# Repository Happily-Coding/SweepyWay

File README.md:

# SweepyWay Split Keyboard 

A truly ergonomic, begginner friendly keyboard.

<details open><summary><h2 style="display:inline-block">Photos & Outputs</h2></summary>

left side | right side
-|-
 | 

[More outputs](https://happily-coding.github.io/SweepyWay/filtered-output/) (images, pdfs, stl 3d models, etc)

<details><summary><h3 style="display:inline-block"> 3D Preview</h3></summary>

The 3D preview shows how the keyboard looks with all components in place (switches, diodes, MCU, and keycaps).

### 3D Model Files

#### Interactive 3D View (STL Format)
- [Left PCB STL](https://happily-coding.github.io/SweepyWay/filtered-output/pcbs/3d/left_pcb-3d.stl) 🎮
- [Right PCB STL](https://happily-coding.github.io/SweepyWay/filtered-output/pcbs/3d/right_pcb-3d.stl) 🎮

> 🎮 **How to View**: Click the links above, then GitHub will automatically render the STL files in an interactive 3D viewer. You can rotate, zoom, and pan using your mouse.

#### Markdown Rendering (ASCII STL)
The ASCII STL files are generated in the workflow and embedded in markdown using the ```stl code block syntax. GitHub renders these automatically when viewing the README.

> 💡 **Note**: The ASCII STL files are generated from the binary STL files in the workflow and embedded directly in this README for instant rendering.

#### STEP Files (CAD Exchange)
- [Left PCB STEP file](https://happily-coding.github.io/SweepyWay/filtered-output/pcbs/3d/left_pcb-3d.step) 🔧
- [Right PCB STEP file](https://happily-coding.github.io/SweepyWay/filtered-output/pcbs/3d/right_pcb-3d.step) 🔧

> ⚠️ **Note**: GitHub doesn't render STEP files directly. Use these for CAD software:
> - Download and open in KiCad 3D viewer, FreeCAD, Fusion 360, etc.
> - Use online STEP viewers like [3DViewer.net](https://3dviewer.net/)
> - Convert to STL format for GitHub rendering

### 3D Rendered Images

left side | right side
-|-
 | 
 | 

### Troubleshooting Missing Components

If the 3D renders show only the PCB without components, the environment variables may not be properly set. The PCB files use `${PATH_TO_SWEEPYWAY_COMPONENT_MODELS}` but KiCad 9 also needs `KICAD9_3DMODEL_DIR`.

**Solution**: Set BOTH environment variables to the same path:
```bash
PATH_TO_SWEEPYWAY_COMPONENT_MODELS="/path/to/component_3d_models" \
KICAD9_3DMODEL_DIR="/path/to/component_3d_models" \
kibot -c kibot/3d_preview.kibot.yaml
```

**GitHub Actions**: The workflow now sets both variables to `${{ github.workspace }}/component_3d_models`

**Verification**: Check that:
1. `component_3d_models/` directory exists
2. All required STEP files are present: `Choc_V1_Hotswap.step`, `Choc_V1_Switch.step`, `Choc_V1_Keycap_MBK_White_1u.step`, etc.
3. The Docker container has access to the models directory

</details>

<details><summary><h3 style="display:inline-block"> Output details</h2></summary>
- Cases contains 3d models (not only of the case), l_cover is the plate that holds the switches firmly in place, and houses the controller and battery, protecting them
<!-- 
?v=1 was used to force the update of the cache from github (it could have been any parameter)
 | 
-->
</details>

<details open><summary><h2 style="display:inline-block">Features</span></summary> 

* **Beginner friendly**
  * Available pdfs, so you can print the layout and see how it feels
  * Abundant keys, but in non disruptive places.
  * No soldering required (WIP)
* **Truly ergonomic**
  * Aggressive column stagger, like Ferris Sweep, to match how fingers are staggered.
  * Choc V1 keys
    * Very low actuation force switches available (example: nocturnal)
    * Low profile (seamless use without handrest, easier to adjust height without an adjustable desk)
    * ChocV1 spacing (reach the outer columns with less over-stretching)
  * Tenting, negative tilting, adjustable height and hand rest solutions (WIP)
* **Energy efficient**
  * [Nice!nano](https://nicekeyboards.com/nice-nano) optimised, but any promicro should work (bottom up) 
  <!-- * [Nice!view](https://nicekeyboards.com/nice-view) support Not tested, probably requires small modifications --> 
  * No leds
* **Accident prepared** 
  * Controller far away from accidental splash zones,
  * Power switch for transport
  * No metal plates to help prevent static discharge from friying the keyboard
  * Hotswappable battery, switches, keycaps, controller, and case. Replace anything that breaks or you dislike.
    * You can even remove the components and use them with a different pcb.
* **Easy to modify** (Declarative design done via yaml)
  * Layout is declared using [Ergogen](https://github.com/mrzealot/ergogen/). 
  * Uses Ergogen to translate YAML to a KiCad PCB and plate files for FR-4 fab or laser cutting
  * Uses Ergogen to output jscad files for the case, and openjscad to convert them to stl.
  * Uses [kicad-automation-scripts](https://github.com/productize/kicad-automation-scripts) and [FreeRouting](https://github.com/freerouting/freerouting) to **automatically route the traces on the PCB**
  * Uses [KiKit](https://github.com/yaqwsx/KiKit) to render PCB previews and production-ready **Gerber files**
  * Uses [Trimesh](https://github.com/mikedh/trimesh/tree/main) to parametrically create a palm rest for the keyboard shape.
  * Uses Kibot to produce jlpcb pos files and BOM so you can order your pcb assembled and not have to solder. (WIP) 
  * Compatible with [no solder spring headers](https://typeractive.xyz/products/no-solder-spring-headers) 

<details><summary><h2 style="display:inline-block"> Work in progress. TODO List</h2></summary>

- perfect top case, and replicate for right side
  - the controller area is delicate, we need to only increase height on the part that the controller and maybe the jsph and reset switch are, since otherwise they wont fit with the plate cutting into them
  - We need to keep the reset butotn exposed to the outside if we want to be able to use the keyboard flash with the cover on (which may be important for typing)
- add the battery and microcontroller 3d model to check there are no issues
- add a lengua in the wall of the case below the top plate to en sure no drainage on the corners?
- Add parametric tenting legs.
- Add spacing between case wall and pcb (add some more padding in addition to the wall thickness)
- Finish making hand rest parametric and integrate it into the pipeline
- Fix the additional outline to cover the controller
- make sure the bom & pos are outputed correctly and ideally automated
- Nice haves:
  - Make base tilting and tenting compatible and or adjustable height
  - add water draining holes
  - Add a piece of plastic that goes inward from the top of the border and fits in it to cover the pcb
  - add leds and spacing for a big batery in the tenting solution
  - add other controller types
  - improve controller pin assignment for better routing
  - Add headers soldering from jlpcb
  - add a tenting system with space for a larger batery or make space for a larger batery in the palm rest, so you can reasonably use the keyboard with rgb.
  - Add row staggered variants that are space efficient.
  - Make sure the keyboard is correctly produced with mbk spacing, and mx spacing.
  - Add the ability to customize keycap spacing for the outer columns and rows
</details>

<details><summary><h2 style="display:inline-block"> How to modify it</h2></summary>

### Setup
If you would like to modify this:
* fork it
* clone it locally with celoide submodule git clone --recurse-submodules https://github.com/Happily-Coding/SweepyWay.git
* change `ergogen/config.yaml` to your liking
* to test it locally if you have node, you can run npm npm i -g ergogen or just npm install from the directory of the repo.
* to be able to view the 3d models in kicad you need go to the top menu -> preferences -> path and add the value for PATH_TO_SWEEPYWAY_COMPONENT_MODELS, which should be the location of your 3d models folder for example C:\Users\YourName\KeyboardDesign\SweepyWay\component_3d_models. Then, after opening kicad , you can open the 3d viewer in the toolbar (or using alt 3).
* to be able to open individual step or stl files, i find [this page](https://3dviewer.net/index.html) comfortable
* to understand what each definition in ergogen ends up creating open the link to the repo [here ](https://ergogen.xyz/)
* reactivate github workflows
* reactivate github pages at https://github.com/your-name/your-repo/settings/pages, choose github actions instead of a branch
* push your changes; the `build.yml` GitHub Workflows(https://github.com/your-name/your-repo/actions) will pick it up, autoroute and generate Gerbers, all in a zip file, and then deploy it to github pages(https://your-name.github.io/your-repo/).
* or:
  * make sure to have Docker CLI and NodeJS installed
  * run `make setup clean all`
  * check the `output` folder for KiCad PCBs and Gerbers
* you can find the latest build artifacts [here](https://happily-coding.github.io/SweepyWay/)

See the [workflow](.github/workflows/build.yml) or the [Makefile](Makefile) for more details.

### Quickly previewing the pcb before pushing
Open the project, open a terminal, run ```cd ergogen``` and ```ergogen .```

### Quickly previewing the case and other jscad files before pushing
Open [neorama openjscad](https://neorama.de/) , and drag the jscad file to the button, you can pan and move using right click or shift rightclick.

### Quickly previewing the palmrest before pushing
- Install uv ```pip install uv``` and run uv sync to generate your virtual environment (only once)
- Run ergogen to produce the outlines.
- ```uv run palmrest_and_tenting_creation/create_palmrest.py```

<!-- 
### Add more keys in places that don't interfere with the controller
Add elements to the row or column matrix, and map them (WIP, TODO explain with more detail)

### Use other controllers

### Use mx switches / chocv2 switches

### Use other battery/reset switches/ footprints
See this examples: 
https://github.com/jsbursik/Janus-Keyboard mx nice nano reversible with custom footprints
https://github.com/tarneaux/triboard xiao controller choc spaced reversible with battery polygon!
https://github.com/Henkru/novum mx with jlpcb target, middle layer for stability, and awesome background art
https://github.com/Musab-Hassan/aurora_keyboard very detailed, and well organized mx example
https://github.com/soundmonster/samoklava/tree/main
https://github.com/christianselig/caldera-keyboard/blob/main/ergogen/config.yaml
https://github.com/jusdisgi/splaveferris/blob/main/ergogen/config.yaml (choc v1, smd) <-- reference for mirrored
https://github.com/jusdisgi/biggie-splays/blob/main/biggie-splays_choc_v1/config.yaml mirror matrix
https://pastebin.com/JzsmATYZ celoide reversible (obtianed from atreus/absolem discord) https://cdn.discordapp.com/attachments/759825860617437204/1376609916986327150/pleiades.yaml?ex=685b8624&is=685a34a4&hm=b6c63e79710fd8ff0cd410843348a5f8570dccdcfe2448ce519ddc2d7e60ecf4&
Complex case, and mounting example with celodie footpritns https://github.com/MalusKnight/SplitMax-Ergogen/blob/main/config.yaml and oleds
https://github.com/Nuclear-Squid/Quacken/blob/main/config.yaml [ro micro non celoide]
https://peterlyons.com/problog/2024/05/kipra-keyboard/ how to load an ergogen otuput to freecad 
https://github.com/johnlamb/LambBT/blob/main/ergogen/config.yaml case, m2 screwes, etc 
https://github.com/AtomicJon/jonkey/blob/main/jonkey-v2.yml other celoide footprints usage
https://github.com/scipioni/clavis alternative stup for auto routing 
#asym in theory can be used in outlines to get only mirrored or only normal points https://docs.ergogen.xyz/outlines/
-->
</details>

<details><summary><h2 style="display:inline-block"> Credits</h2></summary>

- [mxooaar](https://www.reddit.com/r/ErgoMechKeyboards/comments/1lanvon/comment/mxooaar/) for peaking my interest in actually building my idea for a keyboard
- [christianselig caldera keyboard](https://github.com/christianselig/caldera-keyboard) for showing that creating a custom keyboard is reasonably easy
- [Ergogen](https://github.com/ergogen/ergogen) for the awesome tool for building most of the keyboard
- [Soundmonster Samaklova Keyboard](https://github.com/soundmonster/samoklava/tree/main) for automatic electronic routing
- [tbaumann typematrix](https://github.com/tbaumann/typematrix_split_new/tree/main/ergogen) for automatic documentation, and example of how to use celoide ergonomic footprints
- [Celoide](https://github.com/ceoloide/ergogen-footprints) for the library of additional ergogen footprints for more parts and the awesome discord.
- [alakuu/skree](https://www.reddit.com/user/alakuu/) for taking the time to answer questions about pcb assembly services
- [Choco-rain](https://www.reddit.com/r/MechanicalKeyboards/comments/qanrr8/corne_with_3d_printed_cases_wrist_rests_and_plates/) for palmrest inspiration
</details>

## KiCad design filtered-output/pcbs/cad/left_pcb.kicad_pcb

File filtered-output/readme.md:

Where create_palmrest produces its stl if ran locally.

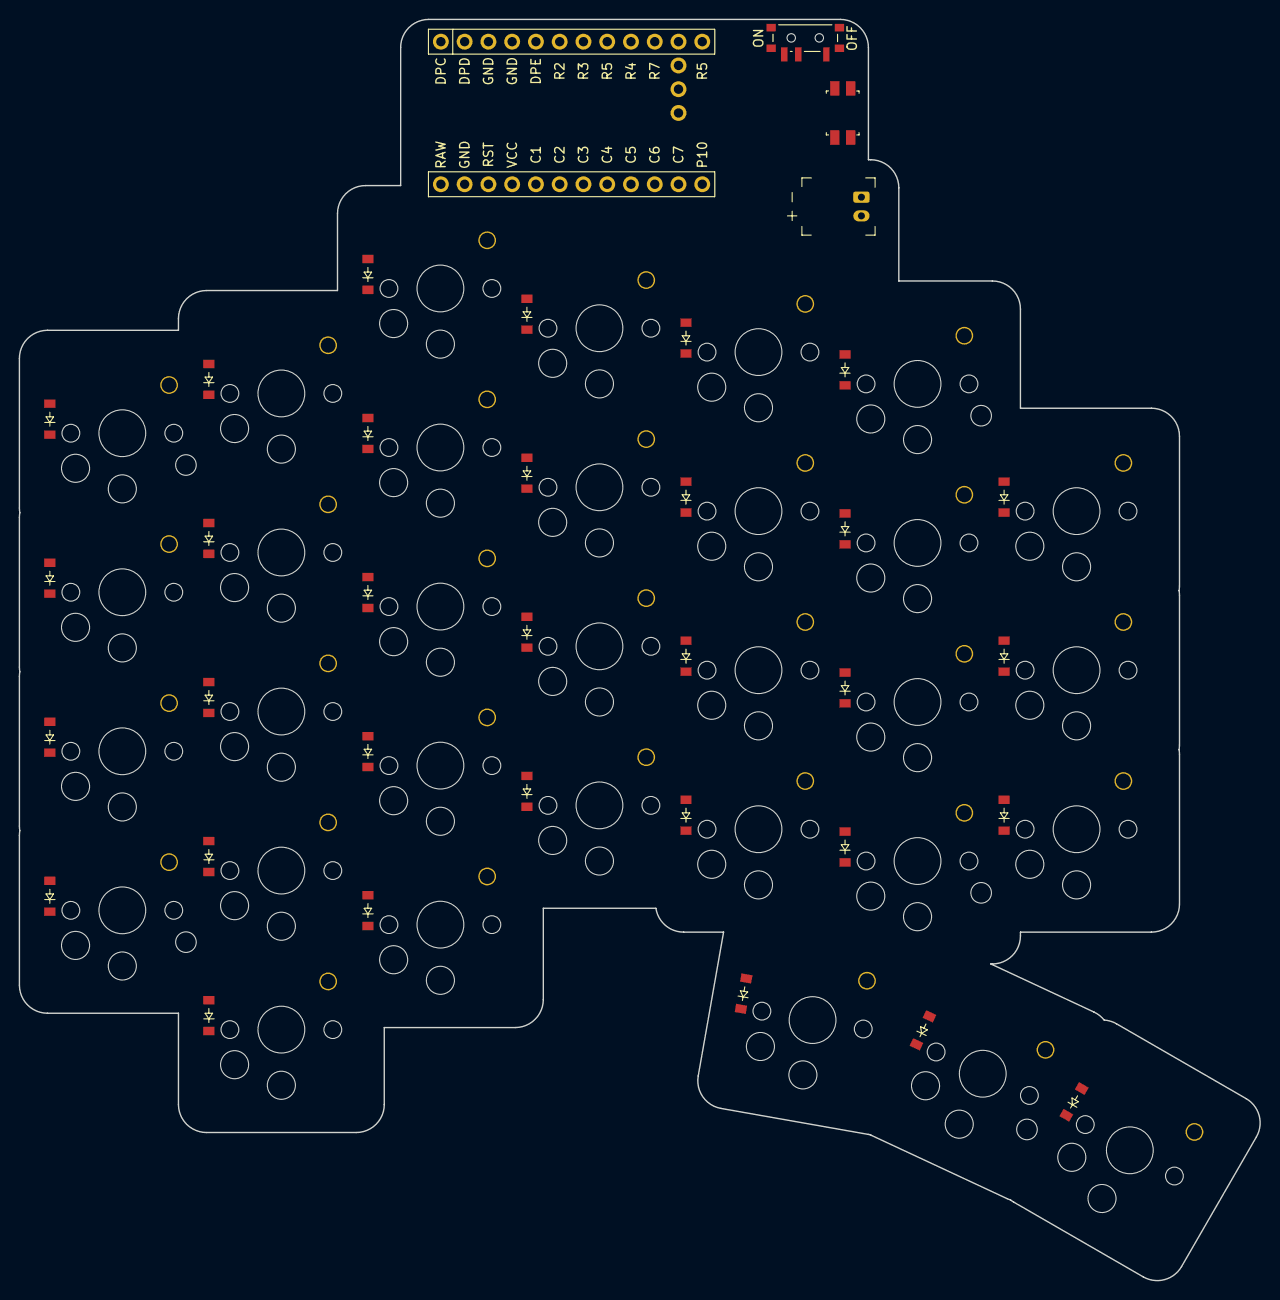
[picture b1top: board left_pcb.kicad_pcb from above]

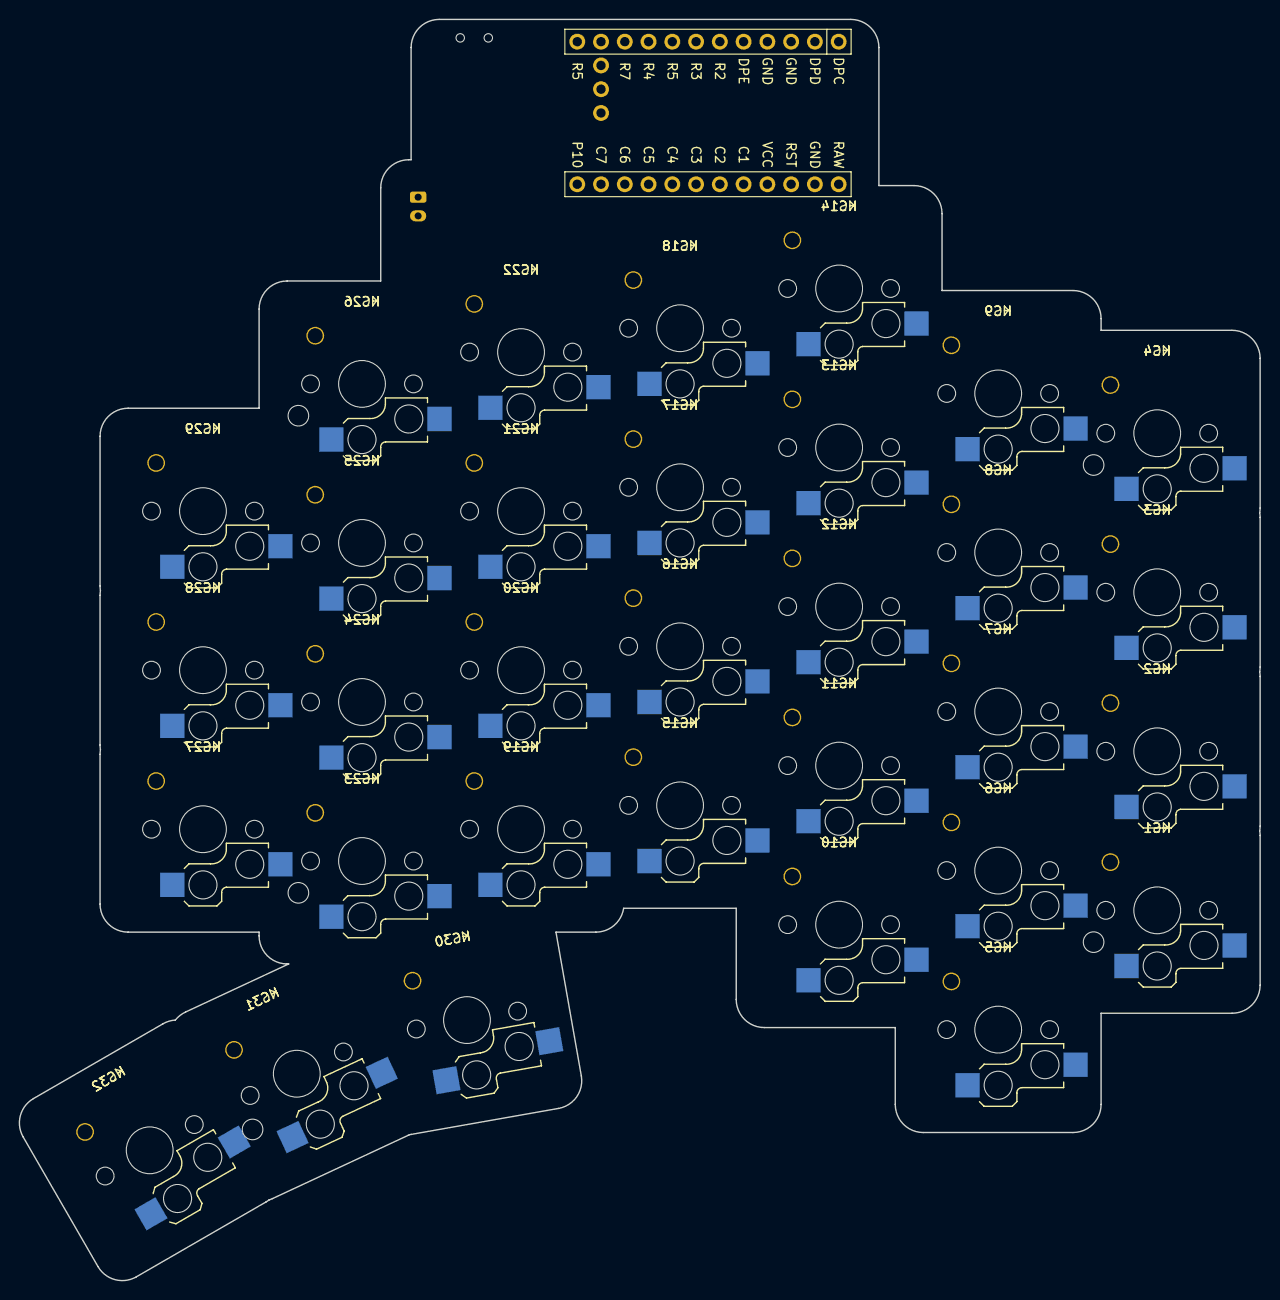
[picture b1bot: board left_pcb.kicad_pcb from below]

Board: 2 copper layers, 132.6 x 134.8 mm, 154 parts (96 on the bottom side), 48 nets, no tracks yet.

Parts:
D1, D2, D3, D4, D5, D6, D7, D8, D9, D10, D11, D12, D13, D14, D15, D16, D17, D18, D19, D20, D21, D22, D23, D24, D25, D26, D27, D28, D29, D30, D31, D32: diode_tht_sod123
H1, H2: header-preview_nano
HS1, HS2, HS3, HS4, HS5, HS6, HS7, HS8, HS9, HS10, HS11, HS12, HS13, HS14, HS15, HS16, HS17, HS18, HS19, HS20, HS21, HS22, HS23, HS24, HS25, HS26, HS27, HS28, HS29, HS30, HS31, HS32: hs-socket-fab-preview_choc_v1_v2
JST1: battery_connector_jst_ph_2
KC1, KC2, KC3, KC4, KC5, KC6, KC7, KC8, KC9, KC10, KC11, KC12, KC13, KC14, KC15, KC16, KC17, KC18, KC19, KC20, KC21, KC22, KC23, KC24, KC25, KC26, KC27, KC28, KC29, KC30, KC31, KC32: keycap-fab-preview_choc_v1_v2
MCU1: mcu_nice_nano
MH1, MH2, MH3, MH4, MH5: mounting_hole_npth
PWR1: power_switch_smd_side
RST1: reset_switch_smd_side
S1, S2, S3, S4, S5, S6, S7, S8, S9, S10, S11, S12, S13, S14, S15, S16, S17, S18, S19, S20, S21, S22, S23, S24, S25, S26, S27, S28, S29, S30, S31, S32: choc_v1_v2
SC1, SC2, SC3, SC4, SC5: screw-preview-top
SC6, SC7, SC8, SC9, SC10: screw-preview-bottom
ST1, ST2, ST3, ST4, ST5: standoff-preview

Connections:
BAT_P: JST1.2, PWR1.3
C1: MCU1.20, S1.2, S2.2, S3.2, S4.2
C2: MCU1.19, S5.2, S6.2, S7.2, S8.2, S9.2
C3: MCU1.18, S10.2, S11.2, S12.2, S13.2, S14.2
C4: MCU1.17, S15.2, S16.2, S17.2, S18.2
C5: MCU1.16, S19.2, S20.2, S21.2, S22.2, S30.2
C6: MCU1.15, S23.2, S24.2, S25.2, S26.2, S31.2
C7: MCU1.14, S27.2, S28.2, S29.2, S32.2
GND: JST1.1, MCU1.3, MCU1.4, MCU1.23, RST1.1, RST1.3
R1: D4.1, D9.1, D14.1, D18.1, D22.1, D26.1
R2: D3.1, D8.1, D13.1, D17.1, D21.1, D25.1, D29.1, MCU1.6
R3: D2.1, D7.1, D12.1, D16.1, D20.1, D24.1, D28.1, MCU1.7
R4: D1.1, D6.1, D11.1, D15.1, D19.1, D23.1, D27.1, MCU1.9
R5: D5.1, D10.1, D30.1, D31.1, D32.1, MCU1.8, MCU1.12
RAW: MCU1.24, PWR1.2
RST: MCU1.22, RST1.2, RST1.4
col1_row1: D4.2, S4.1
col1_row2: D3.2, S3.1
col1_row3: D2.2, S2.1
col1_row4: D1.2, S1.1
col1_thumb_row_1: D30.2, S30.1
col2_row1: D9.2, S9.1
col2_row2: D8.2, S8.1
col2_row3: D7.2, S7.1
col2_row4: D6.2, S6.1
col2_row5: D5.2, S5.1
col2_thumb_row_1: D31.2, S31.1
col3_row1: D14.2, S14.1
col3_row2: D13.2, S13.1
col3_row3: D12.2, S12.1
col3_row4: D11.2, S11.1
col3_row5: D10.2, S10.1
col3_thumb_row_1: D32.2, S32.1
col4_row1: D18.2, S18.1
col4_row2: D17.2, S17.1
col4_row3: D16.2, S16.1
col4_row4: D15.2, S15.1
col5_row1: D22.2, S22.1
col5_row2: D21.2, S21.1
col5_row3: D20.2, S20.1
col5_row4: D19.2, S19.1
col6_row1: D26.2, S26.1
col6_row2: D25.2, S25.1
col6_row3: D24.2, S24.1
col6_row4: D23.2, S23.1
col7_row2: D29.2, S29.1
col7_row3: D28.2, S28.1
col7_row4: D27.2, S27.1

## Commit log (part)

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2025-07-13 added a jlpcb_pos file step to the build action
2025-07-13 commented jlpcb pos file action since autorouting was having issues
2025-07-13 modfied jlcpb pos file to try again
2025-07-13 Tried adding pos file output again
2025-07-13 Removed second iflter
2025-07-13 Attempted to create bom before pos
2025-07-13 modified the pos creator to use an example from an issue
2025-07-13 tried setting the dir in outptus to try to prevent auto route errors
2025-07-14 added bom to jlpcb output
2025-07-14 disabled jlc specific settings to attempt debugging
2025-07-14 fixed a likely issue with the bom code
2025-07-14 removed dir from one part of the bom since it said the option was not found
2025-07-14 moved dir to the other section
2025-07-14 configured dir on the correct place
2025-07-14 commented dir from pick and place file
2025-07-14 reversed changes
2025-07-14 added bom
2025-07-14 moved jlpcb bom to a different file with a different bot version
2025-07-14 removed bom from jlpcb pos and correct jlpcb bom
2025-07-14 changed kibot version to 1 since it seems to be the file definition version
2025-07-15 Tried to ensure autoroute is blocking
2025-07-15 added checks to kibot to try to debug hangs
2025-07-15 commented the breaking bom action
2025-07-15 passed reset switch and power switch to the top
2025-07-15 Tested removing thumb additional area
2025-07-15 commented right thumb outline
2025-07-15 Tried modifiying free routing allowed angles
2025-07-15 separated pinouts in an attempt to make them better
2025-07-26 Started making the hand rest based on the 3d case file.
2025-07-26 better approximation
2025-08-02 Temp additions
2025-08-09 updated reasearch
2025-08-10 Added holes, and started working on a case and cover
2025-08-10 Removed unnecessary comment
2025-08-10 Tried changing the output of generate directory listings to fix github pages gen
2025-08-10 cleaned build.yaml
2025-08-17 Added palm rest experiments and begining of final code
2025-08-17 fixed palmrest name and added a palmrest creation stage to build.yaml
2025-08-17 Moved gitgnore and pyproject.toml to correct place, and clarified steps in build.yaml
2025-08-17 tried not outputing to filtered output
2025-08-17 removed palmrest parametric creation to try to fix actions bug
2025-08-17 Tried updating build.yaml to the previos oune now that last build is a success
2025-08-17 Update create_palmrest.py to not output the file for debugging
2025-08-17 Added a space to force build to be ocnsidered new
2025-08-17 Fixed an issue with create_palmrest.py
2025-08-17 Use celoides autorouting instead of soundmonster
2025-08-17 Added palmrest output
2025-08-17 Fixed output dir
2025-08-17 Tried uncommenting jlpcb bom now that we are using celoides autorouting image
2025-08-17 Updated readme to have collapsible sections
2025-08-17 Improved readme
2025-08-17 Tried to add markdown magic to make headers be collapsible
2025-08-17 Made every section collapsible
2025-08-17 Test
2025-08-17 Improved formatting
2025-08-17 Updated license to match current repo owner
2025-09-20 Added a missing folder for locally running create palm rest
2025-09-20 remove needless uv lock
2025-09-20 updated uv lock
2025-09-20 Ignore fpalm rest locally created models
2025-09-20 Added some bits to start to create the palm rest
2025-09-20 tried removing the mkdir filtered output
2025-09-20 added right half equivalents for most parts
2025-09-20 moved right side componets to the correct side
2025-09-20 fixed usb outline not substracting
2025-09-20 added rtree which somewhy is now considered missing
2025-09-20 standardized and improved microcontroller location and padding
2025-09-20 Added a no soldering required item to description
2025-09-20 forced the refresh of the github readme
2025-09-21 created a preliminary controller area and shifted a part to be able to visualize it easily
2025-09-21 removed the infill from the controller area since it needs to be hollow otherwise there would be no space for the controller
2025-09-21 removed some legacy comments, and added housing for the controller
2025-12-27 Created the first version of the tenting system code
2025-12-27 created the first version of the tilting system code (which is just a backup of the first version of the tenting systme code
2025-12-27 changed the tenting axis to the correct one
2025-12-27 removed cosine smoothing
2025-12-27 Removed tenting exception
2025-12-27 adjusted outdated variable names and comments
2025-12-27 made tenting angle configurable
2025-12-27 hollowed the inside of the shape to save in materials.
2025-12-27 Added the option to add the palm rest to the outline of the base
2025-12-27 added optional inclusion of the palm rest for tenting
2025-12-27 removed create tilting system since the original code already changed too much
2025-12-27 Added a script for visualizing multiple stls at once
2026-01-31 backup current status
2026-01-31 added 3d models for parts
2026-01-31 Tried adding the 3d model for the hotswap footprints
2026-01-31 moved 3d models and first working version (though they are incorrectly placed)
2026-01-31 Added misisng switch, socket, keycap footprints and rotated them to the correct side of the pcb
2026-01-31 Fixed the positioning of the switch 3d model
2026-01-31 Updated readme to include more explanations about the new step files and how to use them
2026-01-31 Expanded readme
2026-02-01 Added multiple 3d models for previsualizaiton
2026-02-01 added 3d model related todos
2026-02-01 updated 3d model related todos
2026-02-01 Added pos file post processing
2026-02-01 Use Happily-Coding fork of ceoloide ergogen-footprints with custom modifications
2026-02-01 Coding plans
2026-02-01 placeholder modificaiton to try to trigger action
2026-02-01 Update submodule to Happily-Coding fork with custom modifications
2026-02-01 ci: add pos file post-processing to build workflow
    Add steps to post-process KiBot-generated POS files for JLCPCB assembly.
    The post-processing script replaces footprint names with JLCPCB part
    numbers (e.g., switch_choc_v1_v2 → CPG135001S30). Processed files are
    copied to filtered-output directory for automatic deployment.
    This change enables automated generation of assembly-ready POS files,
    eliminating manual post-processing steps and ensuring consistent output
2026-02-02 fixed jlpcb pos definition
2026-02-02 attempt to fix pos generation
2026-02-02 another attempt
2026-02-02 next attempt to fix pos
2026-02-02 search for pos
2026-02-02 potentially fixed pos missinlf
2026-02-02 pos fix n
2026-02-03 prepared plans
2026-02-05 Attempted to add 3d preview of the keyboard with components
2026-02-06 attempt to improve 3d rendering
2026-02-06 tried to fix 3d rendering
2026-02-06 try to fix in github 3d rendering
2026-02-06 attempt to fix ascci generation script
2026-02-06 $(cat <<'EOF'
2026-02-06 organized files a bit
2026-02-06 Reorganize GitHub Actions output structure
2026-02-06 Fix permission issues in workflow - add sudo to filtered-output operations
2026-02-06 Fix OpenJSCAD CLI - copy JSCAD files to filtered-output/cases
2026-02-06 Fix permission issues - use sudo only for directory creation, then fix ownership
2026-02-06 Add cascadio
2026-02-06 Fix GLB assembly and STL export issues
2026-02-06 tried to fix 3d visual colors
2026-02-06 3d visualization improvements test
2026-02-06 add examples and fix scaling of the glb
2026-02-06 added file to gitignore
2026-02-07 fix order of actions
2026-02-07 try to fix jscad error
2026-02-07 try to fix the l_cover_stl not found
2026-02-07 fixed orders and namings
2026-02-07 commented right pcb
2026-02-07 Fix the fix glb_scale to not corrupt the glb
2026-02-07 tried modifying the glb export configurations to add the missing components
2026-02-07 Added a few missing details to the pcb export
2026-02-07 added debug print
2026-02-07 fixed 3d_preview to not fail
2026-02-07 Add wrls so that nice nano and evq are rendered in glb
2026-02-07 Add 3dmodels for jstph
2026-02-07 eliminate legacy plans
2026-02-07 update 3d model parts readme
2026-02-07 renamed the files to prevent issues, fixed positioning
2026-02-11 Added hotswap sockets, and keycaps as separate entities so they can be included in the bom and in the pos files, and as separate 3d models on the end result
2026-02-11 Update footprints version to match the changes
2026-02-11 Added chocv2 support
2026-02-13 Corrected keycap position
2026-02-13 Add pin header models
2026-02-13 Add alternative microcontroller models (without wrl)
2026-02-13 add alternative pin header model
2026-02-13 updated models readme
2026-02-14 tried to fix bug with pcb model merging
2026-02-14 Try to fix merge by blutn force
2026-02-14 Promoted the transformation that keeps the correct 3d shape, added a test for one that should keep the inner object structure.
2026-02-14 Try 3 more fixes
2026-02-14 two more tests
2026-02-14 Probably fixed create_full_3d_visual to include all models
2026-02-14 made create_full_3d_visual create to the correct file name
2026-02-15 Added two files that can be used for debugging
2026-02-15 Added transparency to the 3d model and improved posittioning of switch plate a bit
2026-02-15 Added local equivalents to github action workflows
2026-02-15 Fixed mounting hole positions for chocv2
2026-02-15 updated footprints target
2026-02-15 expanded outputs example
2026-02-15 Added basic m2 standoff models
2026-02-15 add screw step models
2026-02-15 added m3 and 2.5 3d models
2026-02-16 Fixed 3d models naming and added missing wrls
2026-02-16 Added missing wrls
2026-02-16 Added more 3d models,. changed ergogen config to use them
2026-02-16 Added headers and adjusted 3d locations of multiple elements
2026-02-16 Add a preliminary version of the sources for m screws and standoffs
2026-02-16 Commit some sucessfull plans that may be used as reference
2026-02-16 Made create_full_3d_visual include tented components output
2026-02-16 Added some missing elements to filtered output
2026-02-16 Added more missing elements to filtered output
2026-02-16 Updated gitignore to avoid some line break encoding difference error
2026-02-16 Ignored some files with too long names
2026-02-16 Closest to working version
2026-02-16 Closest fix
2026-02-16 Finally fixed pcb and pcb components rotation
2026-03-01 Added some shopping links for self reference
2026-03-01 Added some visual references
2026-03-01 Working create 3d visual
2026-03-01 Organized debugging scripts
2026-03-01 created and executed a plan
2026-03-01 updated output
2026-03-07 Added 3d models for the m1.4 and m.16 screws
2026-03-07 Updated todo
2026-03-08 Update submodule to latest commit
2026-03-08 added too large stls to gitignore
2026-03-08 Pin ceoloide submodule to feature/sweepyway-customizations (aff43ae)
2026-03-08 Pin ceoloide submodule back to 87654b4
2026-03-08 Pin ceoloide submodule to aff43ae with restored preview footprints
2026-03-08 Added link to nuts purchase site
2026-03-08 renamed reset switch to standardize
2026-03-08 updated outputs
2026-03-08 Multiple comits with the goal of fixing 3d model preview
